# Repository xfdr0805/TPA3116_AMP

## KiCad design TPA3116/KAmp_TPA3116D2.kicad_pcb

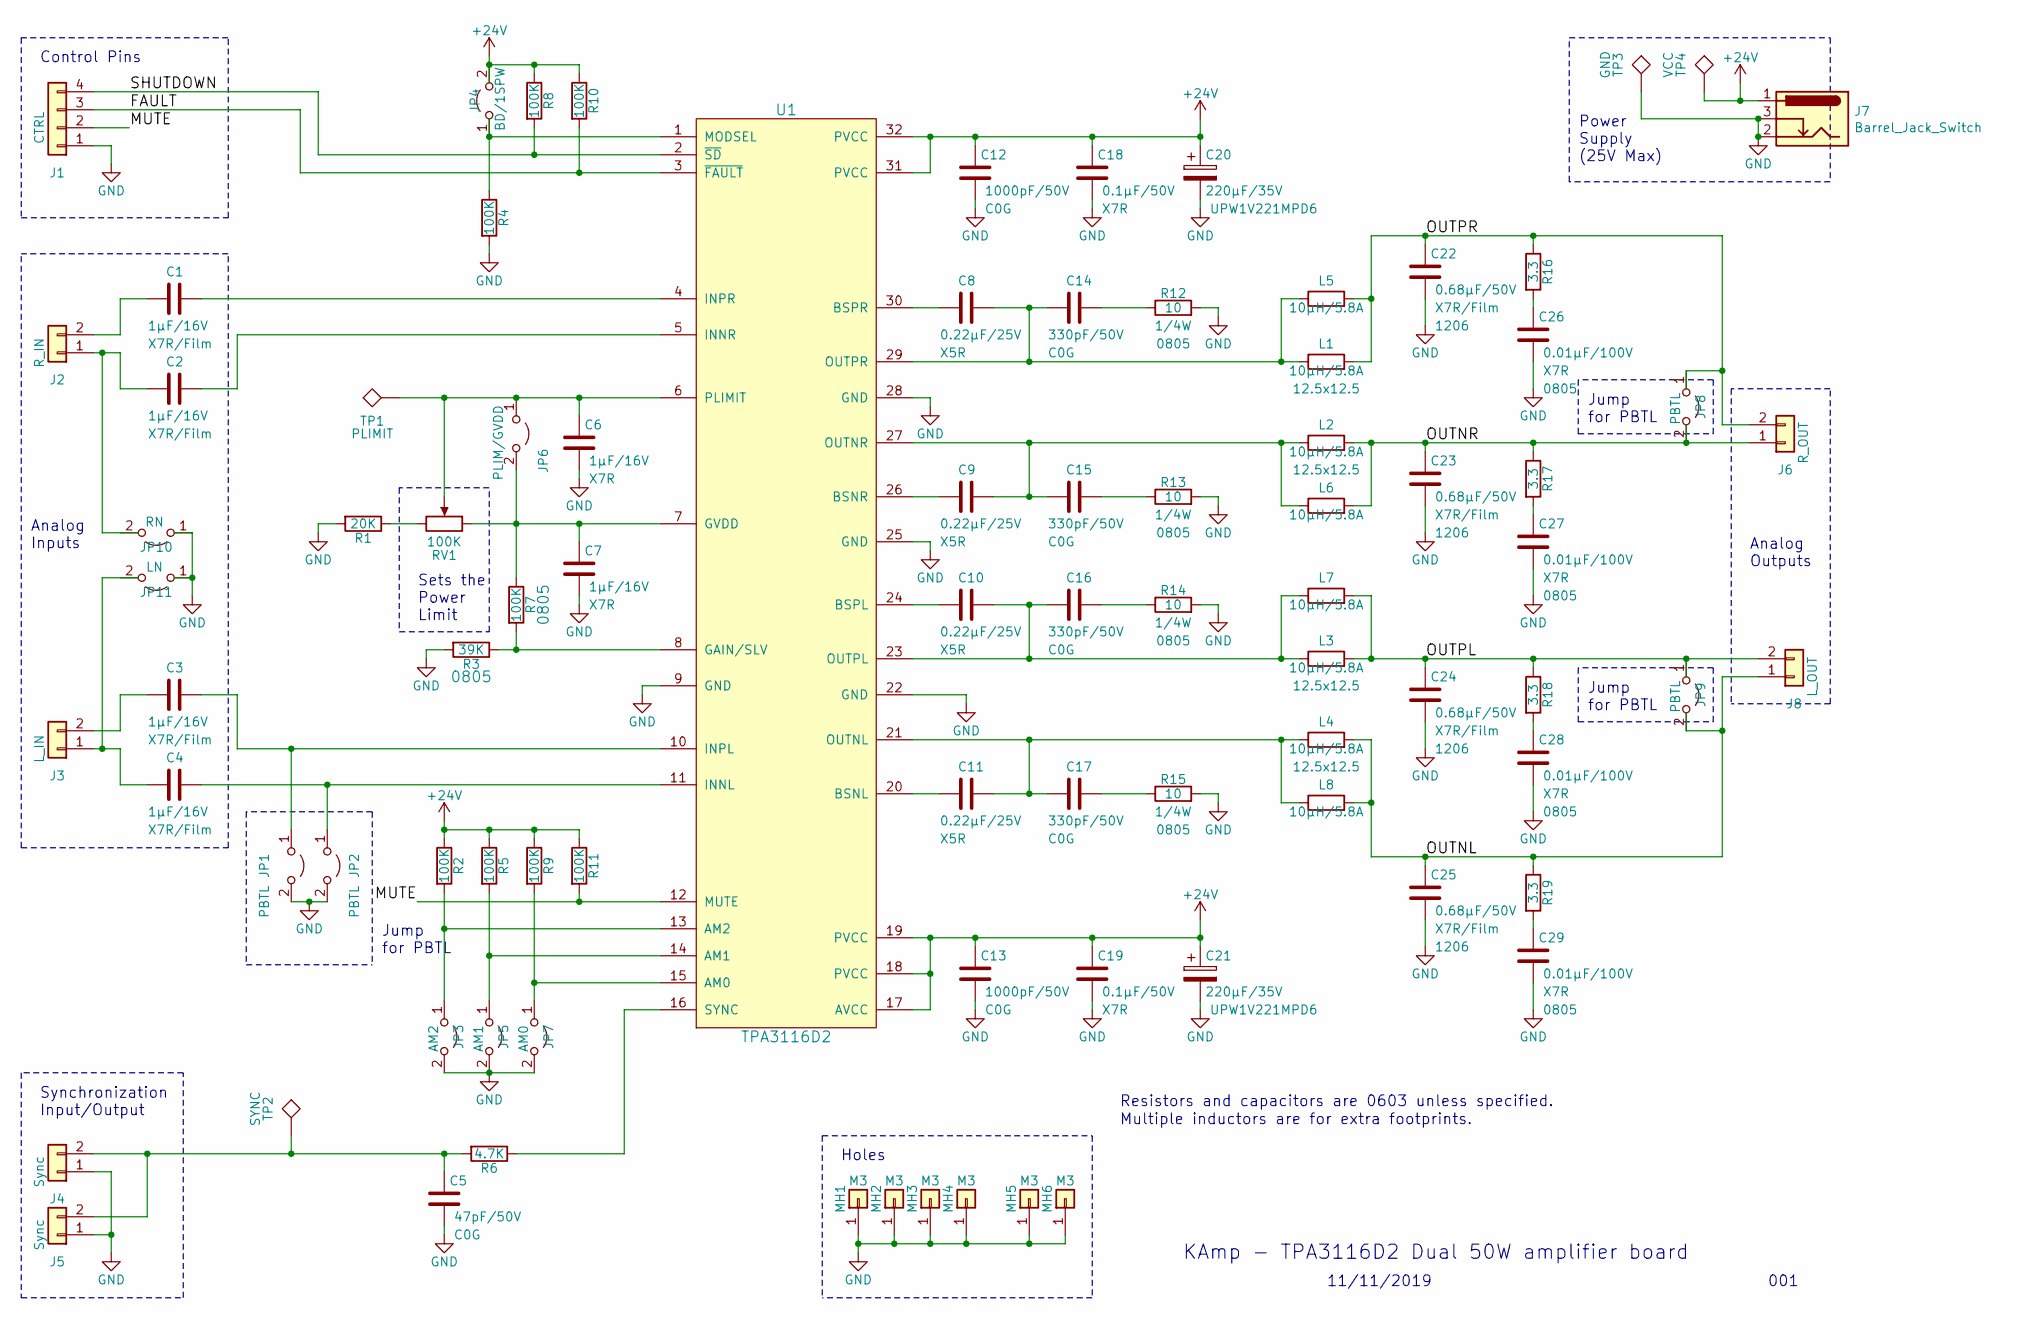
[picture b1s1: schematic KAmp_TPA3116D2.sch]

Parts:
C1, C2, C3, C4: 1µF/16V; C_0603_1608Metric; Rating X7R/Film
C5: 47pF/50V; C_0603_1608Metric; Rating C0G
C6, C7: 1µF/16V; C_0603_1608Metric; Rating X7R
C8, C9, C10, C11: 0.22µF/25V; C_0603_1608Metric; Rating X5R
C12, C13: 1000pF/50V; C_0603_1608Metric; Rating C0G
C14, C15, C16, C17: 330pF/50V; C_0603_1608Metric; Rating C0G
C18, C19: 0.1µF/50V; C_0603_1608Metric; Rating X7R
C20, C21: 220µF/35V; CP_Radial_D8.0mm_P3.50mm
C22, C23, C24, C25: 0.68µF/50V; C_1206_3216Metric; Rating X7R/Film
C26, C27, C28, C29: 0.01µF/100V; C_0805_2012Metric; Rating X7R
J1: CTRL; Molex_KK-254_AE-6410-04A_1x04_P2.54mm_Vertical
J2: R_IN; Molex_KK-254_AE-6410-02A_1x02_P2.54mm_Vertical
J3: L_IN; Molex_KK-254_AE-6410-02A_1x02_P2.54mm_Vertical
J4, J5: Sync; Molex_KK-254_AE-6410-02A_1x02_P2.54mm_Vertical
J6: R_OUT; PhoenixContact_MSTBA_2,5_2-G_1x02_P5.00mm_Horizontal
J7: Barrel_Jack_Switch; BarrelJack_Horizontal
J8: L_OUT; PhoenixContact_MSTBA_2,5_2-G_1x02_P5.00mm_Horizontal
JP1, JP2: PBTL; PinHeader_1x02_P2.54mm_Vertical
JP3: AM2; R_0603_1608Metric
JP4: BD/1SPW; R_0603_1608Metric
JP5: AM1; R_0603_1608Metric
JP6: PLIM/GVDD; R_0603_1608Metric
JP7: AM0; R_0603_1608Metric
JP8, JP9: PBTL; R_Axial_DIN0204_L3.6mm_D1.6mm_P5.08mm_Horizontal
JP10: RN; R_0603_1608Metric
JP11: LN; R_0603_1608Metric
L1, L2, L3, L4: 10µH/5.8A; L_Bourns_SRR1260
L5, L6, L7, L8: 10µH/5.8A; L_Toroid_Horizontal_D11.2mm_P17.00mm_Diameter12-5mm_Amidon-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
MH1, MH2, MH3, MH4: M3; MountingHole_3mm_Pad_Via
MH5, MH6: M3; MountingHole_3mm_Pad
R1: 20K; R_0603_1608Metric
R2, R4, R5, R7, R8, R9, R10, R11: 100K; R_0603_1608Metric
R3: 39K; R_0603_1608Metric
R6: 4.7K; R_0603_1608Metric
R12, R13, R14, R15: 10; R_0603_1608Metric
R16, R17, R18, R19: 3.3; R_0603_1608Metric
RV1: 100K; Potentiometer_Bourns_3314J_Vertical
TP1: PLIMIT; TestPoint_2Pads_Pitch2.54mm_Drill0.8mm
TP2: SYNC; TestPoint_2Pads_Pitch2.54mm_Drill0.8mm
TP3: GND; TestPoint_2Pads_Pitch2.54mm_Drill0.8mm
TP4: VCC; TestPoint_2Pads_Pitch2.54mm_Drill0.8mm
U1: TPA3116D2; HTSSOP-32-1EP_6.1x11mm_P0.65mm_EP5.2x11mm_Mask4.11x4.36mm_T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

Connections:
+24V: C12.1, C13.1, C18.1, C19.1, C20.1, C21.1, J7.1, JP4.2 (B), R2.1, R5.1, R8.1, R9.1, R10.1, R11.1, TP4.1, U1.17 (AVCC), U1.18 (PVCC), U1.19 (PVCC), U1.31 (PVCC), U1.32 (PVCC)
/FAULT: J1.3, R10.2, U1.3 (~FAULT)
/MUTE: J1.2, R11.2, U1.12 (MUTE)
/OUTNL: C25.1, J8.1, JP9.2 (B), L4.2, L8.2, R19.1
/OUTNR: C23.1, J6.1, JP8.2 (B), L2.2, L6.2, R17.1
/OUTPL: C24.1, J8.2, JP9.1 (A), L3.2, L7.2, R18.1
/OUTPR: C22.1, J6.2, JP8.1 (A), L1.2, L5.2, R16.1
/SHUTDOWN: J1.4, R8.2, U1.2 (~SD)
GND: C5.2, C6.2, C7.2, C12.2, C13.2, C18.2, C19.2, C20.2, C21.2, C22.2, C23.2, C24.2, C25.2, C26.2, C27.2, C28.2, C29.2, J1.1, J4.1, J5.1, J7.2, J7.3, JP1.2 (B), JP2.2 (B), JP3.2 (B), JP5.2 (B), JP7.2 (B), JP10.1 (A), JP11.1 (A), MH1.1, MH2.1, MH3.1, MH4.1, MH5.1, MH6.1, R1.2, R3.2, R4.2, R12.2, R13.2, R14.2, R15.2, TP3.1, U1.9 (GND), U1.22 (GND), U1.25 (GND), U1.28 (GND), U1.33 (GND)
unnamed: C1.1, U1.4 (INPR)
unnamed: C1.2, J2.2
unnamed: C2.1, U1.5 (INNR)
unnamed: C2.2, J2.1
unnamed: C3.1, JP1.1 (A), U1.10 (INPL)
unnamed: C3.2, J3.2
unnamed: C4.1, JP2.1 (A), U1.11 (INNL)
unnamed: C4.2, J3.1
unnamed: C5.1, J4.2, J5.2, R6.2, TP2.1
unnamed: C6.1, JP6.1 (A), RV1.2, TP1.1, U1.6 (PLIMIT)
unnamed: C7.1, JP6.2 (B), R7.1, RV1.1, U1.7 (GVDD)
unnamed: C8.2, U1.30 (BSPR)
unnamed: C9.2, U1.26 (BSNR)
unnamed: C10.1, C16.2, L3.1, L7.1, U1.23 (OUTPL)
unnamed: C10.2, U1.24 (BSPL)
unnamed: C11.1, C17.2, L4.1, L8.1, U1.21 (OUTNL)
unnamed: C11.2, U1.20 (BSNL)
unnamed: C14.1, R12.1
unnamed: C8.1, C14.2, L1.1, L5.1, U1.29 (OUTPR)
unnamed: C15.1, R13.1
unnamed: C9.1, C15.2, L2.1, L6.1, U1.27 (OUTNR)
unnamed: C16.1, R14.1
unnamed: C17.1, R15.1
unnamed: C26.1, R16.2
unnamed: C27.1, R17.2
unnamed: C28.1, R18.2
unnamed: C29.1, R19.2
unnamed: JP3.1 (A), R2.2, U1.13 (AM2)
unnamed: JP4.1 (A), R4.1, U1.1 (MODSEL)
unnamed: JP5.1 (A), R5.2, U1.14 (AM1)
unnamed: JP7.1 (A), R9.2, U1.15 (AM0)
unnamed: R1.1, RV1.3
unnamed: R3.1, R7.2, U1.8 (GAIN/SLV)
unnamed: R6.1, U1.16 (SYNC)

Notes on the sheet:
Synchronization Input/Output
Analog Inputs
Jump for PBTL
Control Pins
Power Supply (25V Max)
Analog Outputs
Sets the Power Limit
Holes
KAmp - TPA3116D2 Dual 50W amplifier board
11/11/2019
001
Resistors and capacitors are 0603 unless specified.
Multiple inductors are for extra footprints.

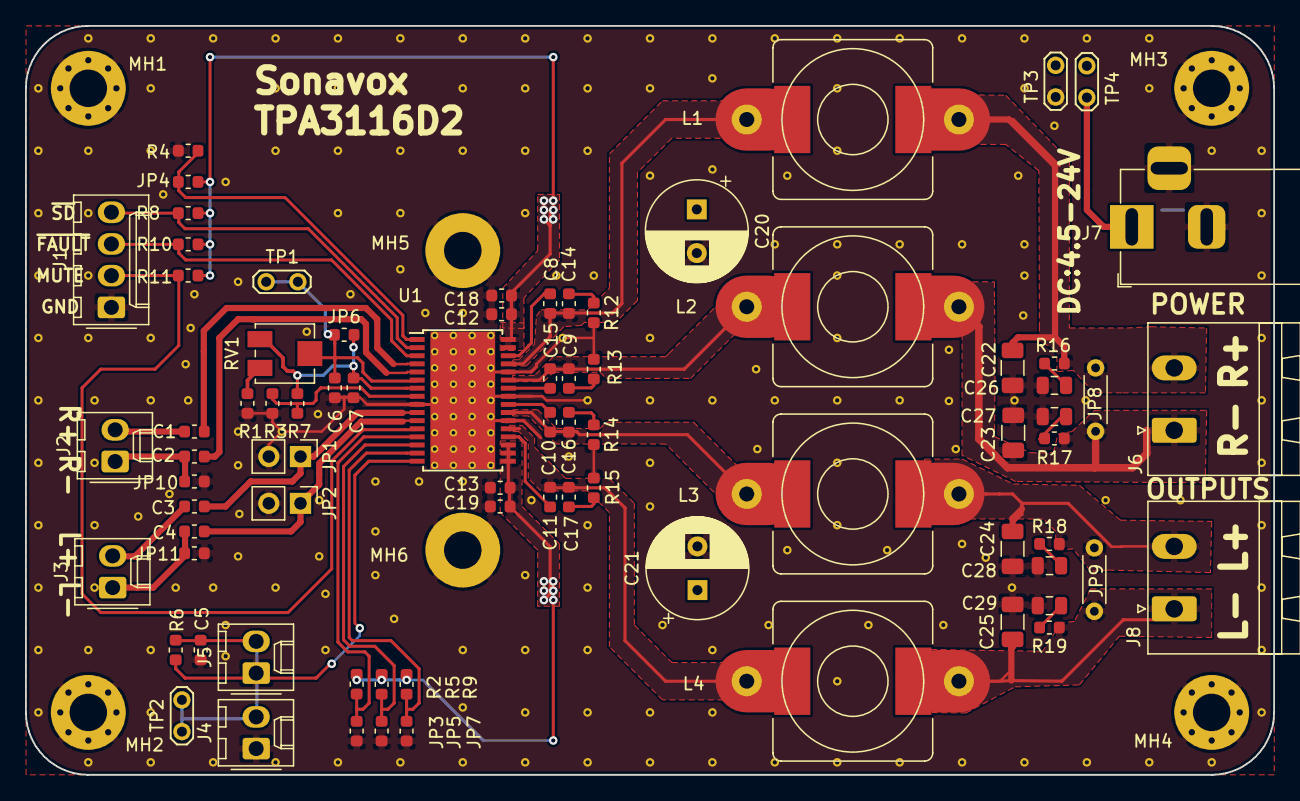
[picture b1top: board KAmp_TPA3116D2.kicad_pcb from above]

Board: 2 copper layers, 100.0 x 60.0 mm, 87 parts (0 on the bottom side), 43 nets.

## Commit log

2019-11-29 修改为Kicad5的版本，并添加了3D封装
2019-11-29 移动到文件夹分类
2019-12-03 将端子向板边延伸2mm
